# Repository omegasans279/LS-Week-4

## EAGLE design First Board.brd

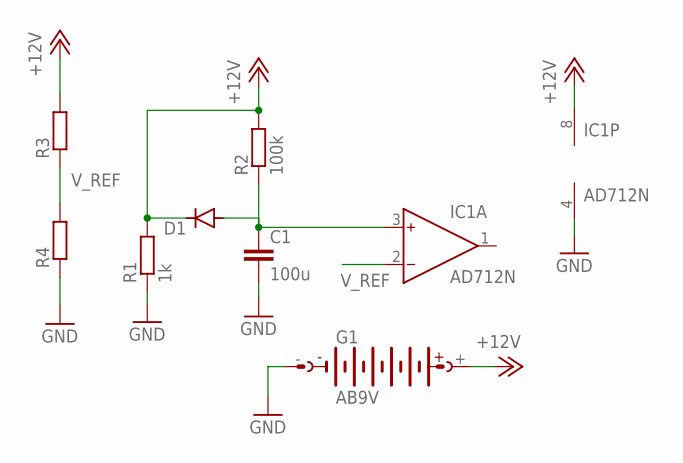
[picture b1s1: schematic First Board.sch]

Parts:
C1: 100u; C0805
D1: DIODE-DO214AC; DO214AC
G1: AB9V
IC1: AD712N; DIL08
R1: 1k; M0805
R2: 100k; M0805
R3, R4: R-EU_M0805; M0805

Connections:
+12V: D1.C, G1.+, IC1.8 (V+), R1.2, R2.2, R3.2
GND: C1.2, G1.-, IC1.4 (V-), R1.1, R4.1
unnamed: C1.1, D1.A, IC1.3 (IN+), R2.1
V_REF: IC1.2 (IN-), R3.1, R4.2

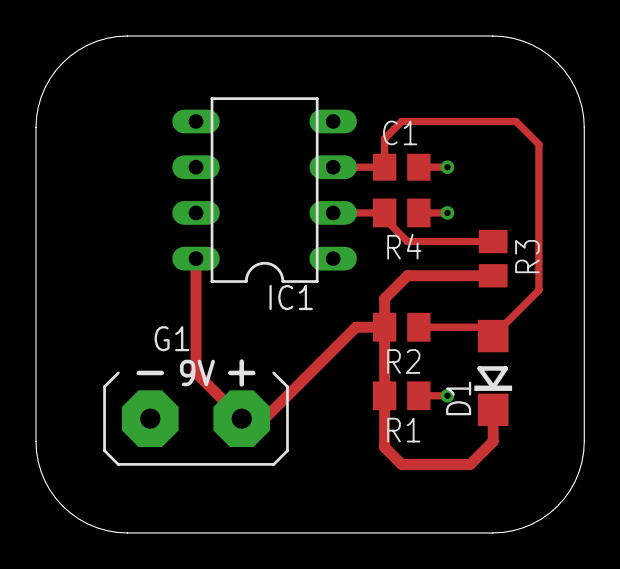
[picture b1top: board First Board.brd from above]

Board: 2 copper layers, 30.5 x 27.6 mm, 8 parts (0 on the bottom side), 4 nets.

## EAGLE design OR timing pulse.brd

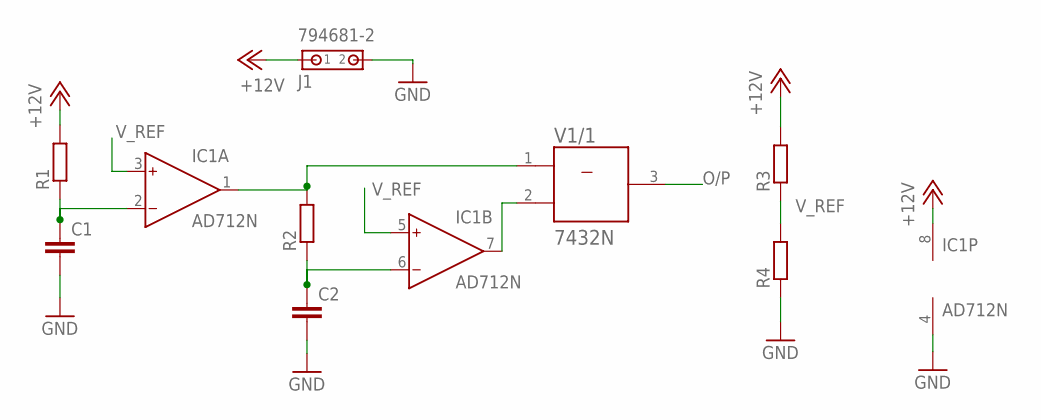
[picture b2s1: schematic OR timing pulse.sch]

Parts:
C1, C2: C-EUC0805; C0805
IC1: AD712N; DIL08
J1: 794681-2
R1, R2, R3, R4: R-EU_R0805; R0805
V1: 7432N; DIL14

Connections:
+12V: IC1.8 (V+), J1.1, R1.2, R3.2
+UB: V1.14 (+UB)
-UB: V1.7 (-UB)
GND: C1.2, C2.2, IC1.4 (V-), J1.2, R4.1
unnamed: C1.1, IC1.2 (IN-), R1.1
unnamed: C2.1, IC1.6 (IN-), R2.1
unnamed: IC1.1 (OUT), R2.2, V1.1 (A)
unnamed: IC1.7 (OUT), V1.2 (B)
O/P: V1.3 (Y)
V_REF: IC1.3 (IN+), IC1.5 (IN+), R3.1, R4.2

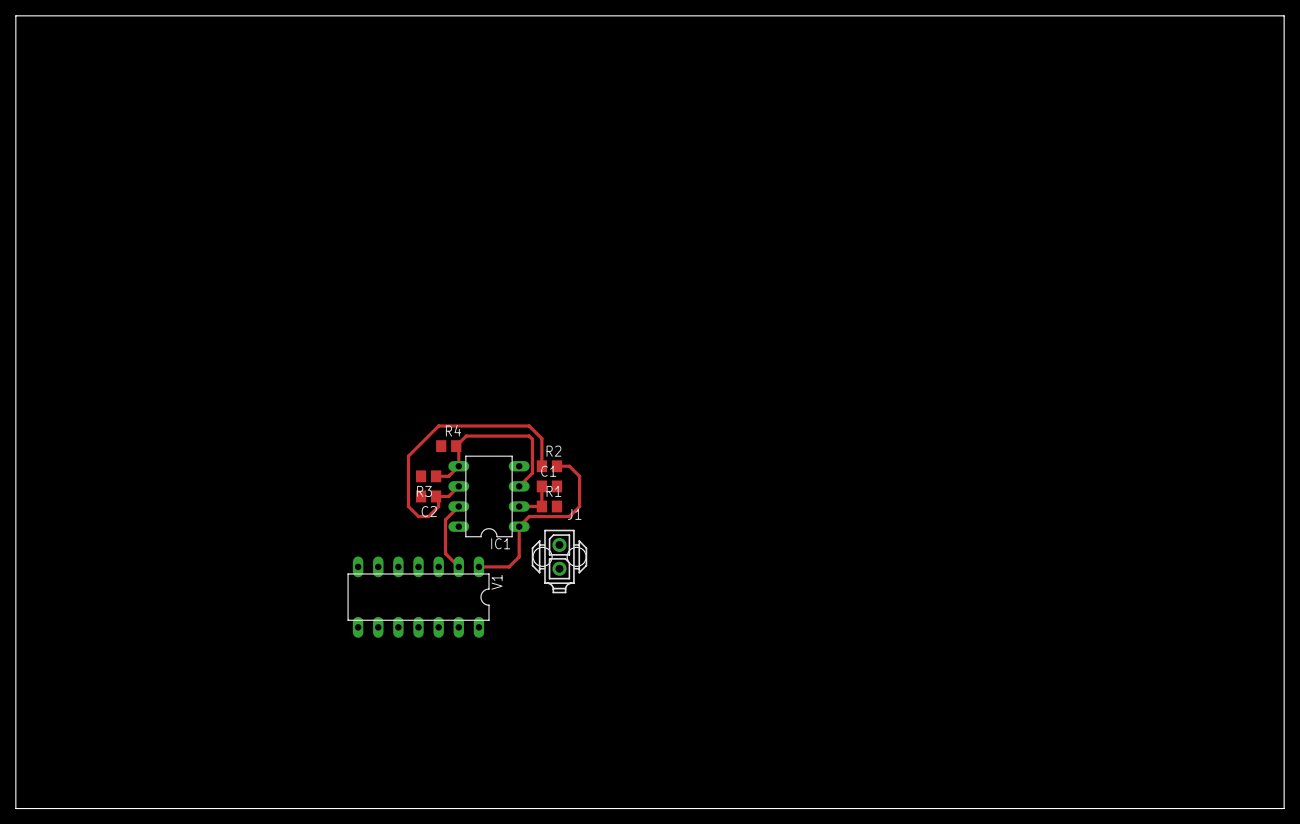
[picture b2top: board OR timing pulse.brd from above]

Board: 2 copper layers, 160.0 x 100.0 mm, 9 parts (0 on the bottom side), 7 nets.

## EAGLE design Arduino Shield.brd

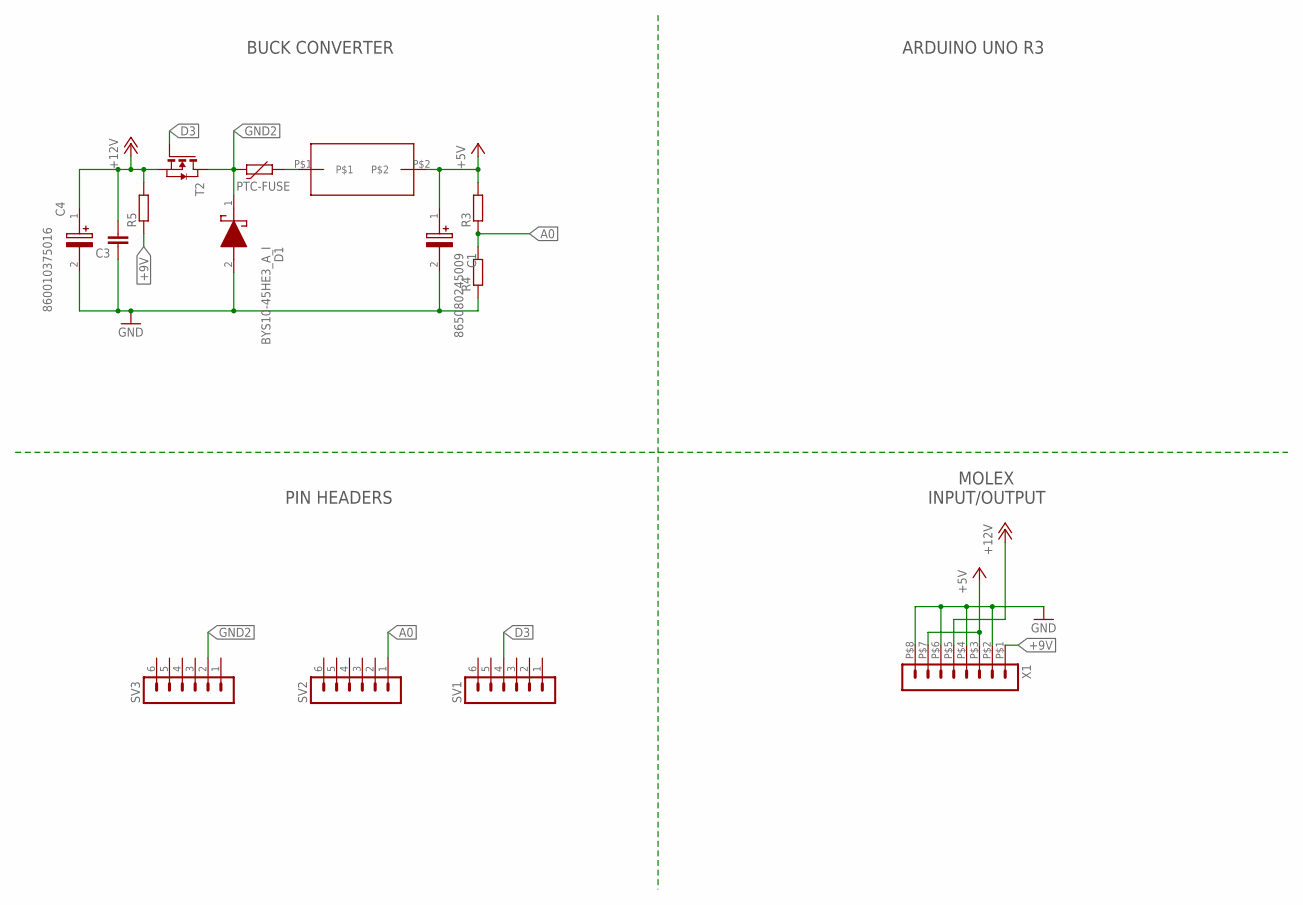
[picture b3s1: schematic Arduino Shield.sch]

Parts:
C1: 865080245009; CAPAE660X770N
C3: C-EUC1206K; C1206K
C4: 860010375016; CAPPRD500W62D1000H1750
D1: BYS10-45HE3_A_I; DIOM5127X229N
FUSE: PTC-FUSE; 1206
R3, R4, R5: R-EU_R1206; R1206
SV1, SV2, SV3: MA06-1_PINHEADERS; MA06-1
T2: NMOSSOT23; SOT-23
U$2: DR1050-INDUCTOR
X1: HEADER_POS8_43045-0812; 43045-0812

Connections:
+5V: C1.1 (+), R3.2, U$2.P$2, X1.P$3 (3), X1.P$7 (7)
+9V: R5.1, X1.P$1 (1)
+12V: C3.2, C4.1 (+), R5.2, T2.2 (S), X1.P$5 (5)
A0: R3.1, R4.2, SV2.1
D3: SV1.4, T2.3 (G)
GND: C1.2 (-), C3.1, C4.2 (-), D1.2 (A), R4.1, X1.P$2 (2), X1.P$4 (4), X1.P$6 (6), X1.P$8 (8)
GND2: D1.1 (K), FUSE.1, SV3.2, T2.1 (D)
unnamed: FUSE.2, U$2.P$1

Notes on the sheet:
BUCK CONVERTER
PIN HEADERS
MOLEX INPUT/OUTPUT
ARDUINO UNO R3

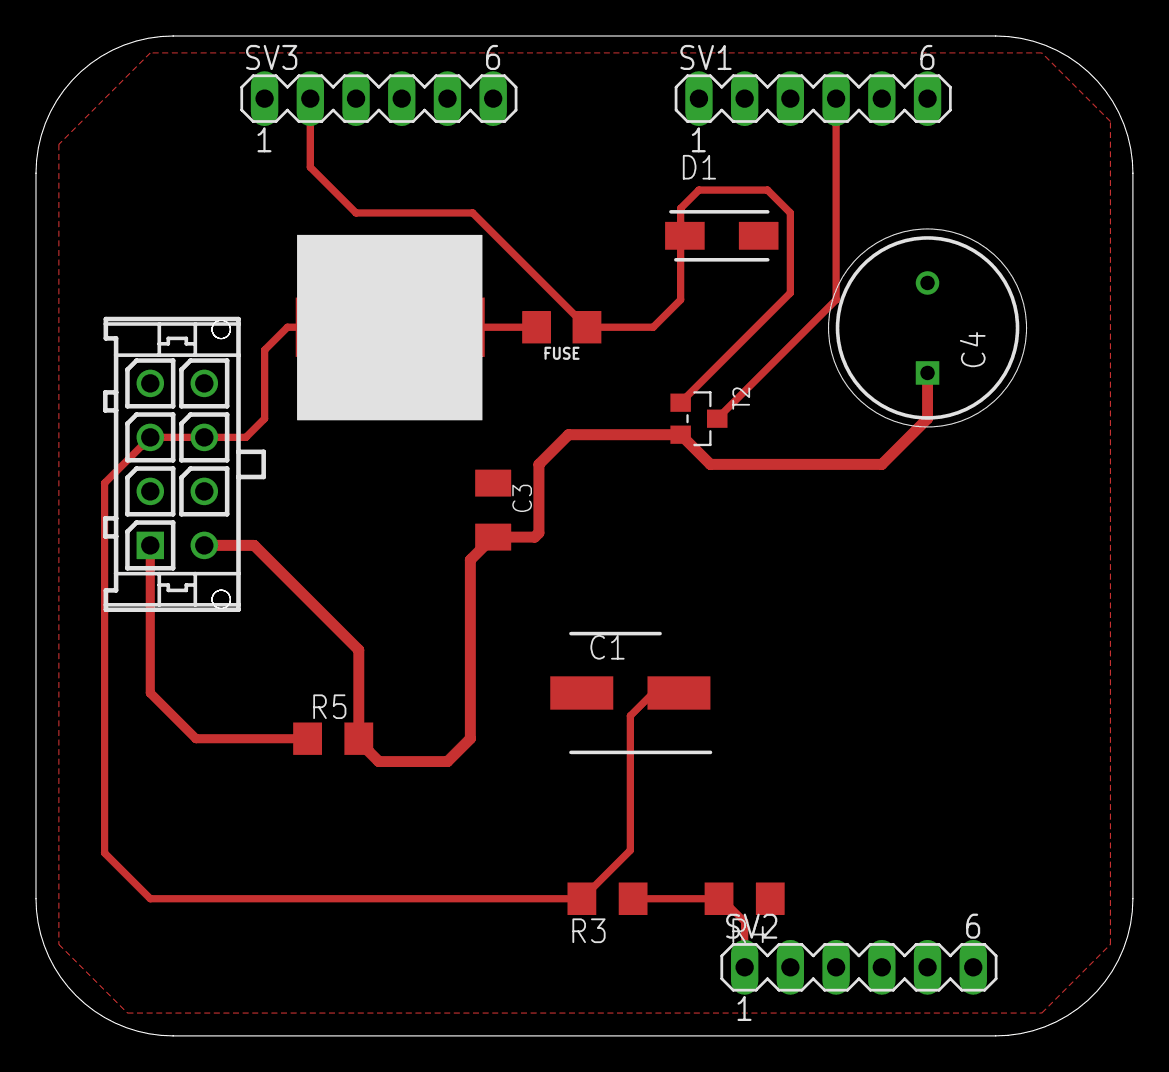
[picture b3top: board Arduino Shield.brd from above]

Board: 2 copper layers, 60.9 x 55.5 mm, 14 parts (0 on the bottom side), 8 nets.

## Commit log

2024-07-30 Created using Colab
2024-09-30 Create delme
